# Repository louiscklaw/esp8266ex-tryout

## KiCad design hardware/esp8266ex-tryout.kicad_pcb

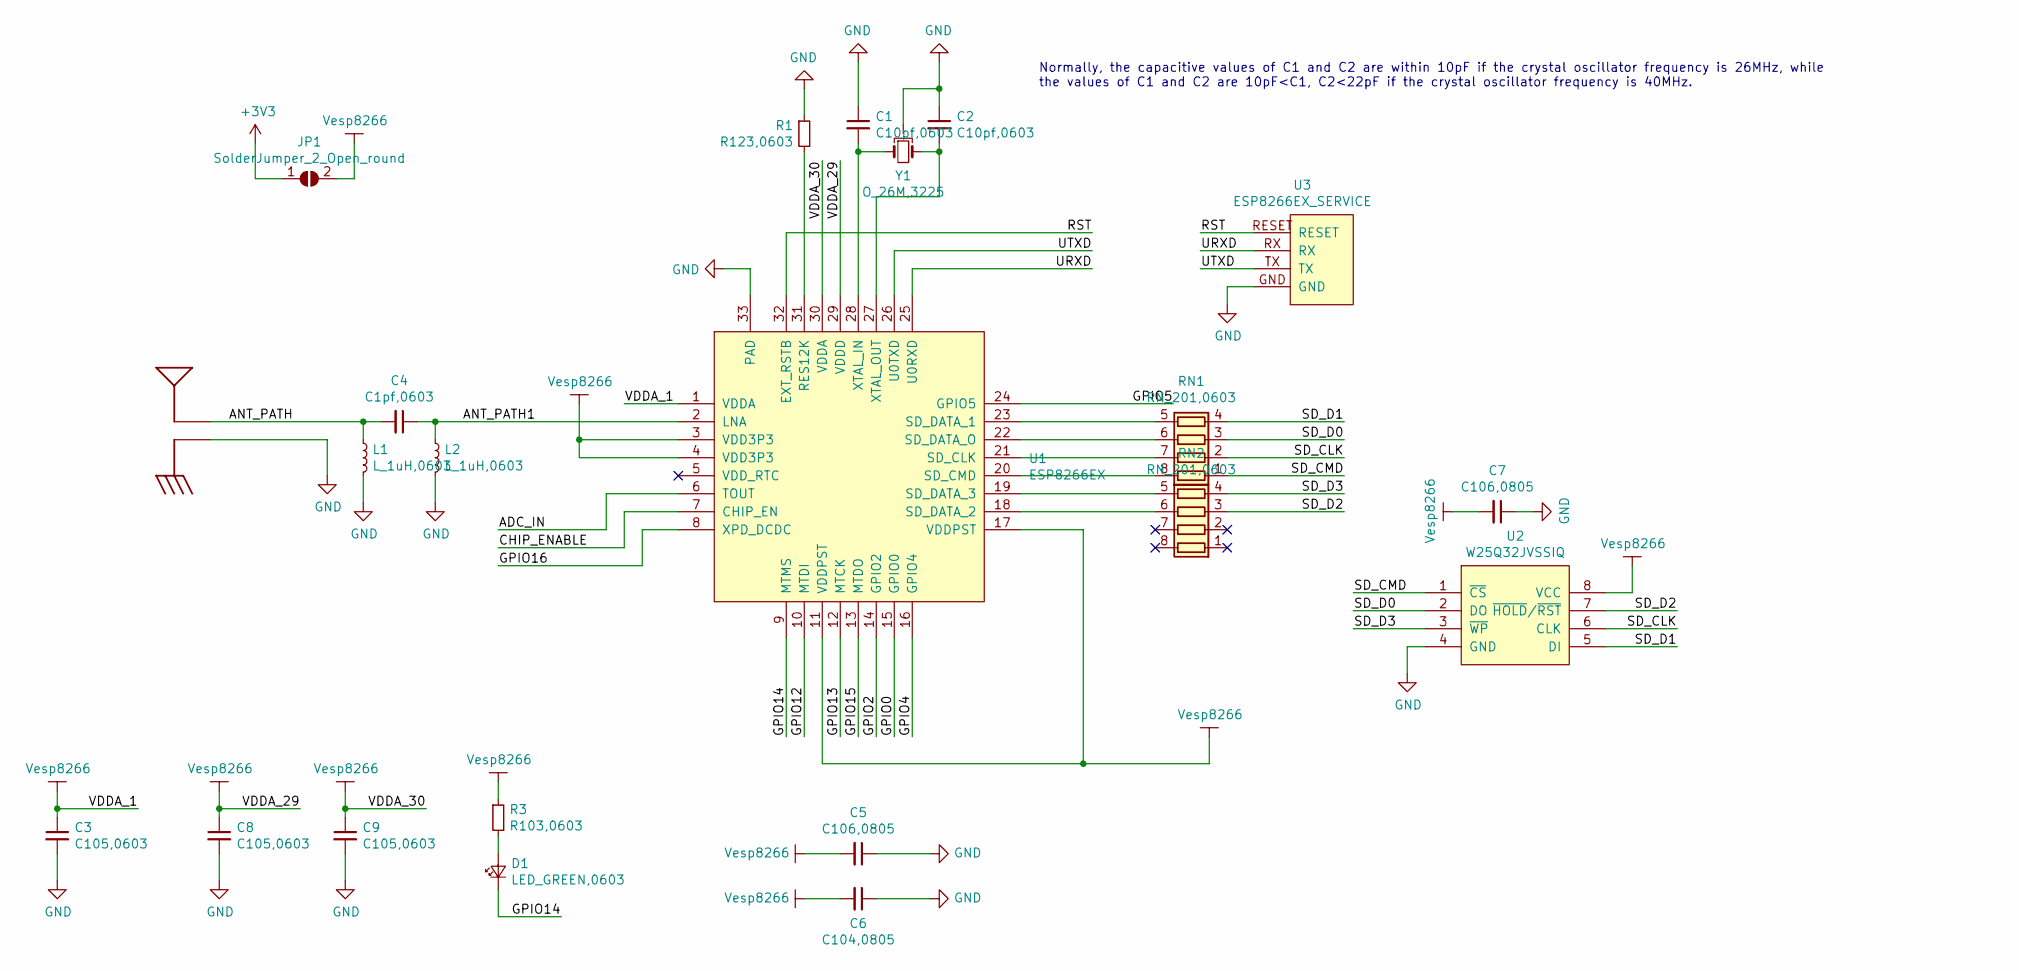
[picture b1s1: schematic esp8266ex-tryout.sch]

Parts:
ANT1: AN9520
C1, C2: C10pf,0603; C_0603_1608Metric_Pad1.05x0.95mm_HandSolder
C3, C8, C9: C105,0603; C_0603_1608Metric_Pad1.05x0.95mm_HandSolder
C4: C1pf,0603; C_0603_1608Metric_Pad1.05x0.95mm_HandSolder
C5, C7: C106,0805; C_0805_2012Metric_Pad1.15x1.40mm_HandSolder
C6: C104,0805; C_0805_2012Metric_Pad1.15x1.40mm_HandSolder
D1: LED_GREEN,0603; LED_0603_1608Metric
JP1: SolderJumper_2_Open_round; SolderJumper-2_P1.3mm_Open_RoundedPad1.0x1.5mm
L1, L2: L_1uH,0603; L_0603_1608Metric_Pad1.05x0.95mm_HandSolder
R1: R123,0603; R_0603_1608Metric_Pad1.05x0.95mm_HandSolder
R3: R103,0603; R_0603_1608Metric_Pad1.05x0.95mm_HandSolder
RN1, RN2: RN_201,0603; R_Array_Concave_4x0603
U1: ESP8266EX
U2: W25Q32JVSSIQ
U3: ESP8266EX_SERVICE
Y1: O_26M,3225; OSC_3225

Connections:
+3V3: JP1.1 (A)
/ADC_IN: U1.6 (TOUT)
/ANT_PATH: ANT1.P$FEED (FEED), C4.2, L1.1
/ANT_PATH1: C4.1, L2.1, U1.2 (LNA)
/CHIP_ENABLE: U1.7 (CHIP_EN)
/GPIO0: U1.15 (GPIO0)
/GPIO2: U1.14 (GPIO2)
/GPIO4: U1.16 (GPIO4)
/GPIO5: U1.24 (GPIO5)
/GPIO12: U1.10 (MTDI)
/GPIO13: U1.12 (MTCK)
/GPIO14: D1.1 (K), U1.9 (MTMS)
/GPIO15: U1.13 (MTDO)
/GPIO16: U1.8 (XPD_DCDC)
/RST: U1.32 (EXT_RSTB), U3.RESET
/SD_CLK: RN1.2 (R2.1), U2.6 (CLK); also elsewhere on the board
/SD_CMD: RN1.1 (R1.1), U2.1 (~CS~)
/SD_D0: RN1.3 (R3.1), U2.2 (DO)
/SD_D1: RN1.4 (R4.1), U2.5 (DI)
/SD_D2: RN2.3 (R3.1), U2.7 (~HOLD~/~RST~)
/SD_D3: RN2.4 (R4.1), U2.3 (~WP~)
/URXD: U1.25 (U0RXD), U3.RX
/UTXD: U1.26 (U0TXD), U3.TX
GND: ANT1.P$GND (GND), C1.1, C2.1, C3.2, C5.1, C6.1, C7.1, C8.2, C9.2, L1.2, L2.2, R1.1, U1.33 (PAD), U2.4 (GND), U3.GND, Y1.2
unnamed: C1.2, U1.28 (XTAL_IN), Y1.1
unnamed: C2.2, U1.27 (XTAL_OUT), Y1.3
unnamed: D1.2 (A), R3.2
unnamed: R1.2, U1.31 (RES12K)
unnamed: RN1.5 (R4.2), U1.23 (SD_DATA_1)
unnamed: RN1.6 (R3.2), U1.22 (SD_DATA_O)
unnamed: RN1.7 (R2.2), U1.21 (SD_CLK)
unnamed: RN1.8 (R1.2), U1.20 (SD_CMD)
unnamed: RN2.5 (R4.2), U1.19 (SD_DATA_3)
unnamed: RN2.6 (R3.2), U1.18 (SD_DATA_2)
Vesp8266: C3.1, C5.2, C6.2, C7.2, C8.1, C9.1, JP1.2 (B), R3.1, U1.1 (VDDA), U1.3 (VDD3P3), U1.4 (VDD3P3), U1.11 (VDDPST), U1.17 (VDDPST), U1.29 (VDDD), U1.30 (VDDA), U2.8 (VCC)

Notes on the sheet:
Normally, the capacitive values of C1 and C2 are within 10pF if the crystal oscillator frequency is 26MHz, while the values of C1 and C2 are 10pF<C1, C2<22pF if the crystal oscillator frequency is 40MHz.

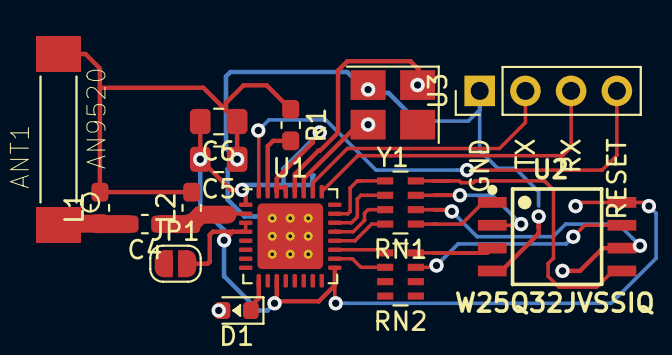
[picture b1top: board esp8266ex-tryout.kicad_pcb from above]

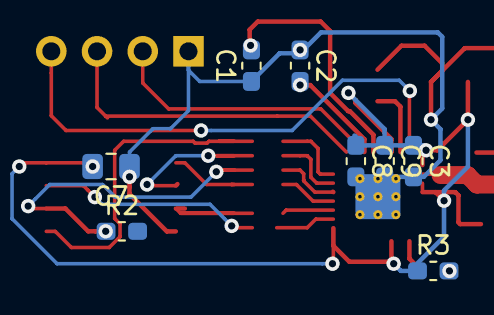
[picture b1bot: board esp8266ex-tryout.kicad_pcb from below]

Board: 2 copper layers, 23 parts (8 on the bottom side), 24 nets.

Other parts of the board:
R2: R201,0603; R_0603_1608Metric_Pad1.05x0.95mm_HandSolder

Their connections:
/SD_CLK: R2.1; also elsewhere on the board

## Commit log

2019-06-07 update,
2019-06-08 update to add debug ,
2019-06-08 update for RN,
2020-05-05 ci: init travis build config,
2020-05-05 ci: init travis token,
